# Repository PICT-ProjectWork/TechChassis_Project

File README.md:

# TechChassis_Project
Developed TechChassis, an autonomous robot designed to move on its own, avoid obstacles, and handle loads smoothly. Using ROS2 Humble, Gazebo, and RViz2, created and tested the full navigation system, including mapping, localization, path planning, and motion control. Used sensor fusion with LiDAR, IMU, and wheel encoder data to make the robot’s movement more accurate and stable. All functions were tested through simulations to ensure reliable navigation in changing environments. Also designed the robot’s chassis in Fusion 360 and prepared the embedded control setup using STM32CubeIDE and Arduino IDE for future hardware implementation.

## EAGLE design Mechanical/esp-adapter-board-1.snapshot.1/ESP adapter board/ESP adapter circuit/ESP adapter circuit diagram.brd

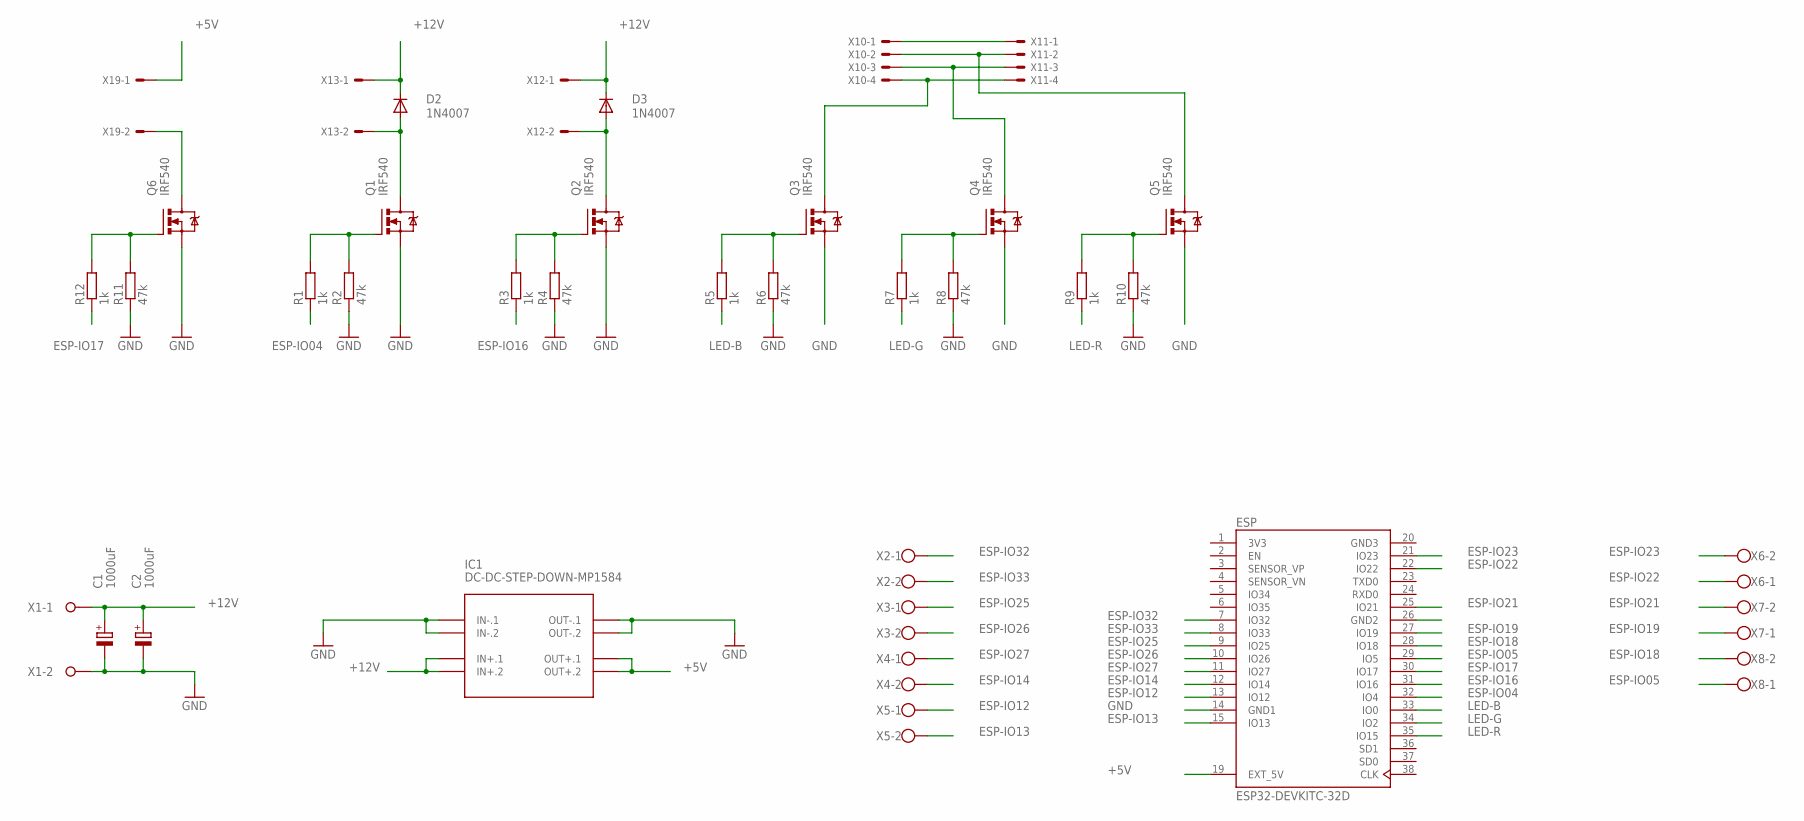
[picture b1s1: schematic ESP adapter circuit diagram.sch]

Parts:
C1, C2: 1000uF; E5-13
D2, D3: 1N4007; DO41-10
ESP: ESP32-DEVKITC-32D; MODULE_ESP32-DEVKITC-32D
IC1: DC-DC-STEP-DOWN-MP1584
Q1, Q2, Q3, Q4, Q5, Q6: IRF540; TO220BV
R1, R3, R5, R7, R9, R12: 1k; 0204/7
R2, R4, R6, R8, R10, R11: 47k; 0204/7
X1: GND; W237-132
X2, X3, X4, X5, X6, X7, X8: W237-102
X10, X11: 22-27-2041-04; 6410-04
X12, X13, X19: 22-27-2021-02; 6410-02

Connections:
3V3: ESP.1 (3V3)
+5V: ESP.19 (EXT_5V), IC1.OUT+.1, IC1.OUT+.2, X19.1
+12V: C1.+, C2.+, D2.C, D3.C, IC1.IN+.1, IC1.IN+.2, X1.1, X10.1, X11.1, X12.1, X13.1
ESP-IO04: ESP.32 (IO4), R1.1
ESP-IO05: ESP.29 (IO5), X8.1
ESP-IO12: ESP.13 (IO12), X5.1
ESP-IO13: ESP.15 (IO13), X5.2
ESP-IO14: ESP.12 (IO14), X4.2
ESP-IO16: ESP.31 (IO16), R3.1
ESP-IO17: ESP.30 (IO17), R12.1
ESP-IO18: ESP.28 (IO18), X8.2
ESP-IO19: ESP.27 (IO19), X7.1
ESP-IO21: ESP.25 (IO21), X7.2
ESP-IO22: ESP.22 (IO22), X6.1
ESP-IO23: ESP.21 (IO23), X6.2
ESP-IO25: ESP.9 (IO25), X3.1
ESP-IO26: ESP.10 (IO26), X3.2
ESP-IO27: ESP.11 (IO27), X4.1
ESP-IO32: ESP.7 (IO32), X2.1
ESP-IO33: ESP.8 (IO33), X2.2
GND: C1.-, C2.-, ESP.14 (GND1), IC1.IN-.1, IC1.IN-.2, IC1.OUT-.1, IC1.OUT-.2, Q1.S, Q2.S, Q3.S, Q4.S, Q5.S, Q6.S, R2.1, R4.1, R6.1, R8.1, R10.1, R11.1, X1.2
GND3: ESP.20 (GND3)
LED-B: ESP.33 (IO0), R5.1
LED-G: ESP.34 (IO2), R7.1
LED-R: ESP.35 (IO15), R9.1
unnamed: Q1.G, R1.2, R2.2
unnamed: Q2.G, R3.2, R4.2
unnamed: Q3.G, R5.2, R6.2
unnamed: D2.A, Q1.D, X13.2
unnamed: Q5.D, X10.2, X11.2
unnamed: Q6.G, R11.2, R12.2
unnamed: Q3.D, X10.4, X11.4
unnamed: Q4.D, X10.3, X11.3
unnamed: Q4.G, R7.2, R8.2
unnamed: Q5.G, R9.2, R10.2
unnamed: Q6.D, X19.2
unnamed: D3.A, Q2.D, X12.2

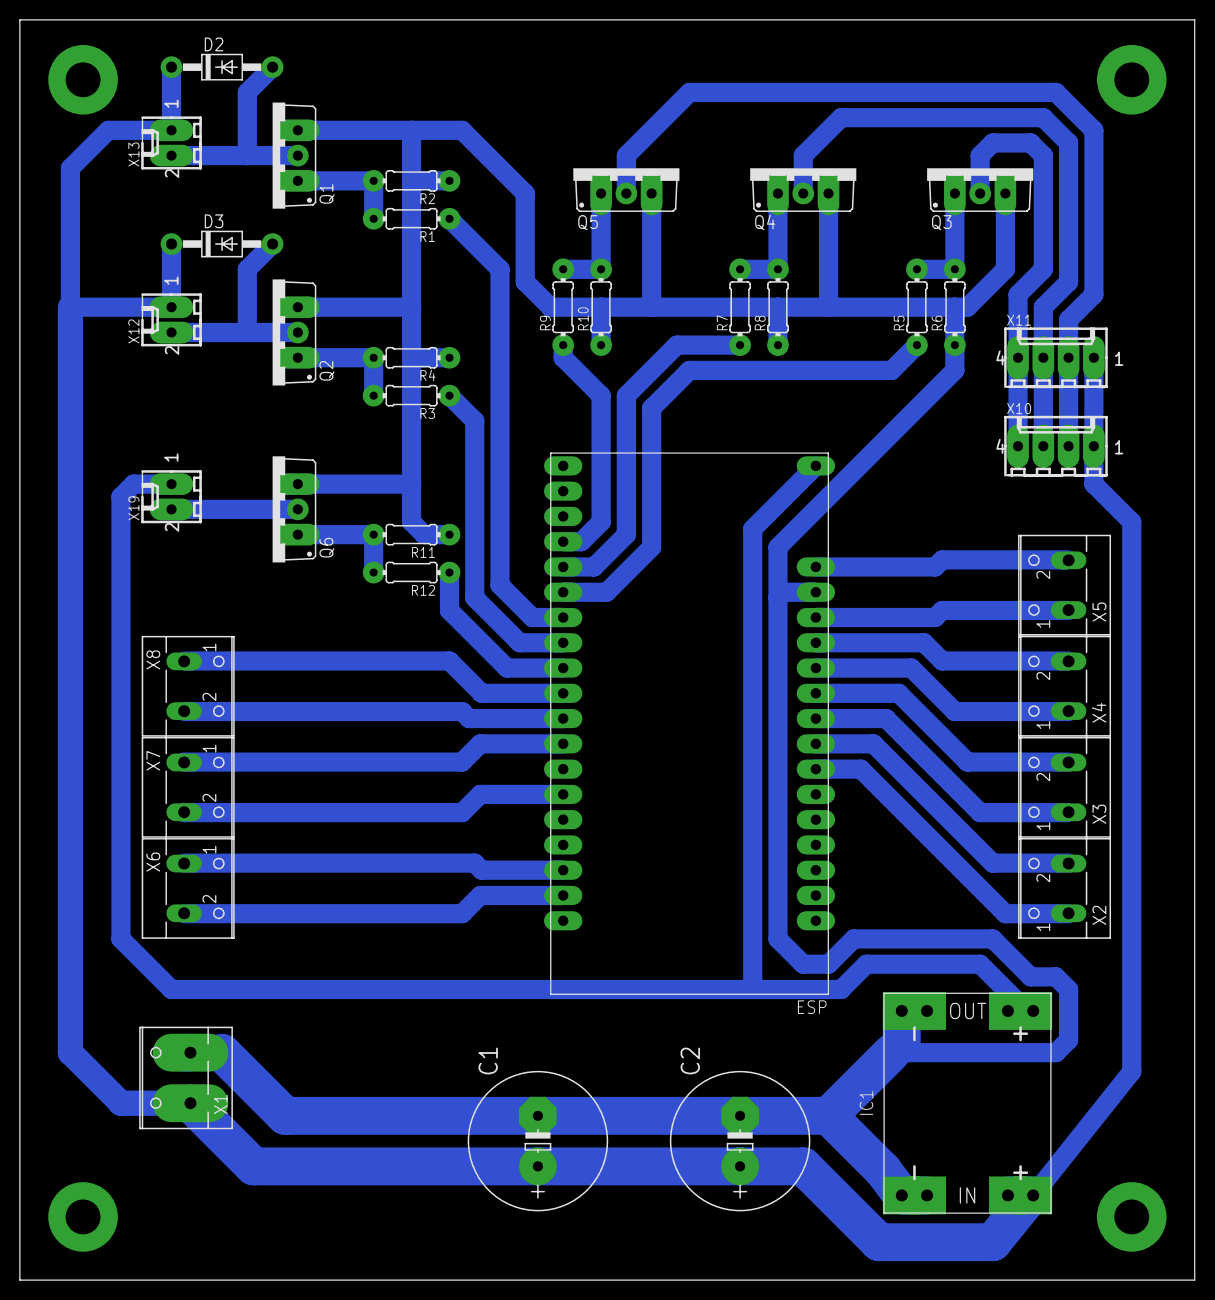
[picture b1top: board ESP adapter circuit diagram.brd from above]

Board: 2 copper layers, 118.1 x 126.7 mm, 37 parts (0 on the bottom side), 35 nets.

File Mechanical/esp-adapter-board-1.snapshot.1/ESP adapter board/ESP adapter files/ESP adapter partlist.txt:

Partlist

Exported from ESP adapter circuit diagram.brd at 09.07.2020 17:51:51

EAGLE Version 7.2.0 Copyright (c) 1988-2014 CadSoft

Assembly variant: 

Part     Value                  Package                  Library                 Position (mm)         Orientation

C1       1000uF                 E5-13                    rcl                     (80.01 45.72)         R90
C2       1000uF                 E5-13                    rcl                     (100.33 45.72)        R90
D2       1N4007                 DO41-10                  diode                   (48.26 153.67)        R0
D3       1N4007                 DO41-10                  diode                   (48.26 135.89)        R0
ESP      ESP32-DEVKITC-32D      MODULE_ESP32-DEVKITC-32D ESP32-DEVKITC-32D-final (95.25 87.63)         R180
IC1      DC-DC-STEP-DOWN-MP1584 DC-DC-STEP-DOWN-MP1584   diy-modules             (123.19 49.53)        R90
Q1       IRF540                 TO220BV                  transistor-power        (53.34 144.78)        R90
Q2       IRF540                 TO220BV                  transistor-power        (53.34 127)           R90
Q3       IRF540                 TO220BV                  transistor-power        (124.46 143.51)       R0
Q4       IRF540                 TO220BV                  transistor-power        (106.68 143.51)       R0
Q5       IRF540                 TO220BV                  transistor-power        (88.9 143.51)         R0
Q6       IRF540                 TO220BV                  transistor-power        (53.34 109.22)        R90
R1       1k                     0204/7                   rcl                     (67.31 138.43)        R180
R2       47k                    0204/7                   rcl                     (67.31 142.24)        R180
R3       1k                     0204/7                   rcl                     (67.31 120.65)        R180
R4       47k                    0204/7                   rcl                     (67.31 124.46)        R180
R5       1k                     0204/7                   rcl                     (118.11 129.54)       R90
R6       47k                    0204/7                   rcl                     (121.92 129.54)       R90
R7       1k                     0204/7                   rcl                     (100.33 129.54)       R90
R8       47k                    0204/7                   rcl                     (104.14 129.54)       R90
R9       1k                     0204/7                   rcl                     (82.55 129.54)        R90
R10      47k                    0204/7                   rcl                     (86.36 129.54)        R90
R11      47k                    0204/7                   rcl                     (67.31 106.68)        R180
R12      1k                     0204/7                   rcl                     (67.31 102.87)        R180
X1       GND                    W237-132                 con-wago-508            (44.45 52.07)         R90
X2                              W237-102                 con-wago-500            (132.08 71.12)        R90
X3                              W237-102                 con-wago-500            (132.08 81.28)        R90
X4                              W237-102                 con-wago-500            (132.08 91.44)        R90
X5                              W237-102                 con-wago-500            (132.08 101.6)        R90
X6                              W237-102                 con-wago-500            (45.72 71.12)         R270
X7                              W237-102                 con-wago-500            (45.72 81.28)         R270
X8                              W237-102                 con-wago-500            (45.72 91.44)         R270
X10      22-27-2041-04          6410-04                  con-molex               (132.08 115.57)       R0
X11      22-27-2041-04          6410-04                  con-molex               (132.08 124.46)       R0
X12      22-27-2021-02          6410-02                  con-molex               (43.18 128.27)        R90
X13      22-27-2021-02          6410-02                  con-molex               (43.18 146.05)        R90
X19      22-27-2021-02          6410-02                  con-molex               (43.18 110.49)        R90

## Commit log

2026-01-21 Project Status Updated
2026-01-21 Project Updated

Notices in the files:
parts and their libraries:
diy-modules: Released under the Creative Commons Attribution 4.0 International License: http://creativecommons.org/licenses/by/4.0
